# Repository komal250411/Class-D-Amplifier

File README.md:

# Class D Audio Amplifier
**Developed by:** Komal Dudhbhate

### Description
This project is a high-efficiency Class D Audio Amplifier designed in KiCad. It uses Pulse Width Modulation (PWM) to drive a MOSFET output stage, followed by an LC filter to recreate clear analog sound.

### Technical Highlights
* **High-Speed Comparator:** Uses the ADA4898 for sharp PWM edges to reduce heat and distortion.
* **Optimized Power Paths:** All high-current tracks are **1.5mm wide** to handle power safely without overheating.
* **EMI Protection:** A solid bottom ground plane was implemented to shield the audio signal from switching noise.
* **Output Filter:** Designed with a $22\mu H$ inductor and $1\mu F$ capacitor for a clean **33.9 kHz** cutoff frequency.

###  Navigate this Repo
* **Class D.pdf**: Schematic diagram of the circuit.
* **Class D.kicad_pcb**: The physical board layout.
* **Gerber Files**: Production-ready files for manufacturing.
* **Class D.csv**: Bill of Materials (BOM).

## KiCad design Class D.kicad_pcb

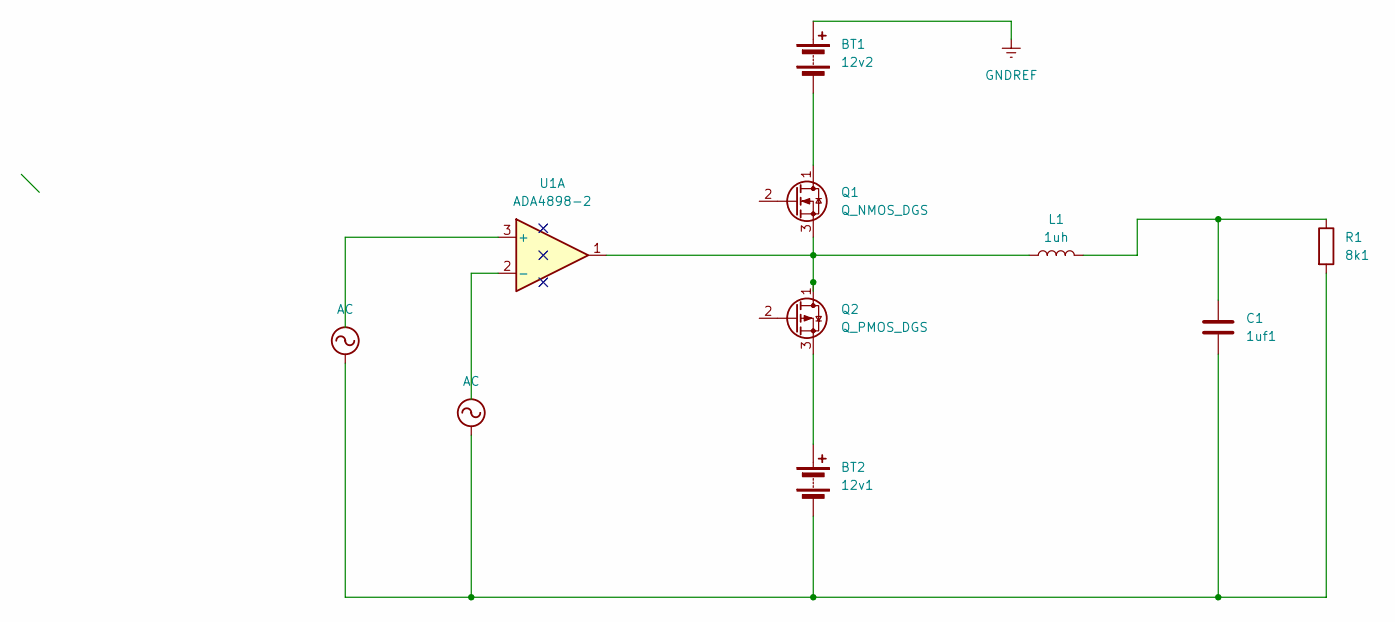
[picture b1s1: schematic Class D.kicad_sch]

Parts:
BT1: 12v2; PinHeader_1x02_P2.54mm_Vertical
BT2: 12v1; PinHeader_1x02_P2.54mm_Vertical
C1: 1uf1; C_Rect_L7.2mm_W3.0mm_P5.00mm_FKS2_FKP2_MKS2_MKP2
L1: 1uh; L_Toroid_Vertical_L16.0mm_W8.0mm_P7.62mm
Q1: Q_NMOS_DGS; TO-220-3_Vertical
Q2: Q_PMOS_DGS; TO-220-3_Vertical
R1: 8k1; R_Axial_DIN0207_L6.3mm_D2.5mm_P7.62mm_Horizontal
U1: ADA4898-2; DIP-8_W7.62mm

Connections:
AC: BT2.2 (-), C1.2, R1.2
GNDREF: BT1.1 (+)
unnamed: BT1.2 (-), Q1.1 (D)
unnamed: BT2.1 (+), Q2.3 (S)
unnamed: C1.1, L1.2, R1.1
unnamed: L1.1, Q1.3 (S), Q2.1 (D), U1.1

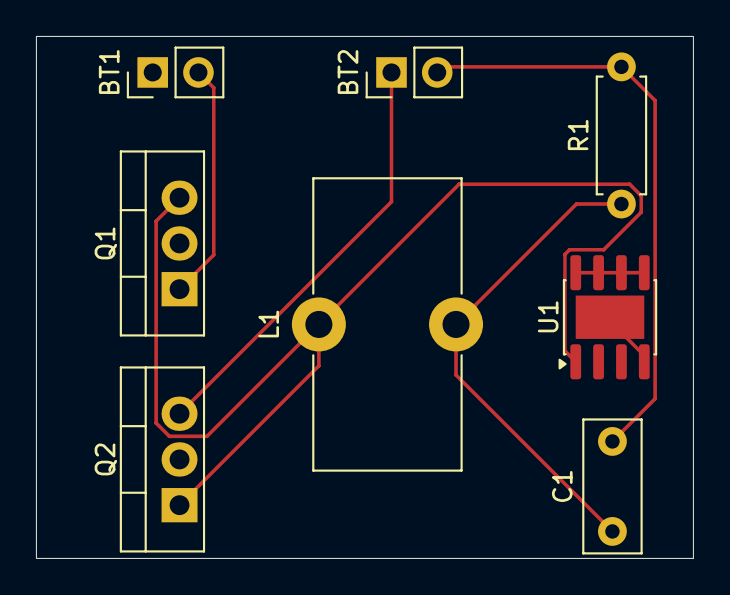
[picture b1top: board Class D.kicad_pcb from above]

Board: 2 copper layers, 36.5 x 29.0 mm, 8 parts (0 on the bottom side), 5 nets.

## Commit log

2025-12-24 Revise README with project details and navigation
    Updated project title and added detailed description, technical highlights, and navigation instructions.
